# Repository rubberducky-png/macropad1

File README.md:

# rektek macropad
It has 9 keys (9 switches), a rotary encoder, and an OLED display. Each key is backlit with SK6812 MINI-E LEDs. It uses [QMK](https://qmk.fm/) firmware

## CAD Model:
Everything is connected by four M3x16mm screws and M3x5mx4mm heatset inserts. The case is printed in two parts, top and bottom.

<p align="center">
  <strong>Made in onShape</strong>
</p>

## PCB:
<p align="center">
  Schematic
</p>

<br>
<p align="center">
  PCB
</p>

<p align="center">
  <strong>Made in KiCad</strong>
</p>

## Case:

<p align="center">
  <strong>Made in onShape</strong>
</p>

## Firmware:
This Hackpad uses KMK.
#   Row 1: Rewind          Play/Pause      Fast Forward
#   Row 2: Netflix         Spotify         VS Code
#   Row 3: Left             Right           LED Mode Cycle

</p>

## Final result:
<p align="center">
 TBD
</p>
<p align="center">
    <b>HACKPAD DEMO WILL BE HERE</b>
  </a>
</p>
I really enjoyed creating my own hackpad, I learned how to create PCBs and schematics in KiCAD. There were a few mistakes in the model, but I was able to fix them pretty easily

## BOM:
Here is everything you need to create this Hackpad:
| Component | Amount |
| :--- | :---: |
| **Seeed XIAO RP2040** | 1x |
| **MX-Style switches** | 9x |
| **1N4148 Diodes** | 9x | 
| **EC11 Rotary encoder** | 1x |
| **0.91 inch OLED display** | 1x |
| **DSA keycaps** | 9x |
| **SK6812 MINI-E LED** | 12x |
| **M3x16mm screw** | 4x |
| **M3x5mx4mm heatset insert** | 4x |
| **Case** (2 printed parts) | 1x |
| **PCB** | 1x |

<hr>

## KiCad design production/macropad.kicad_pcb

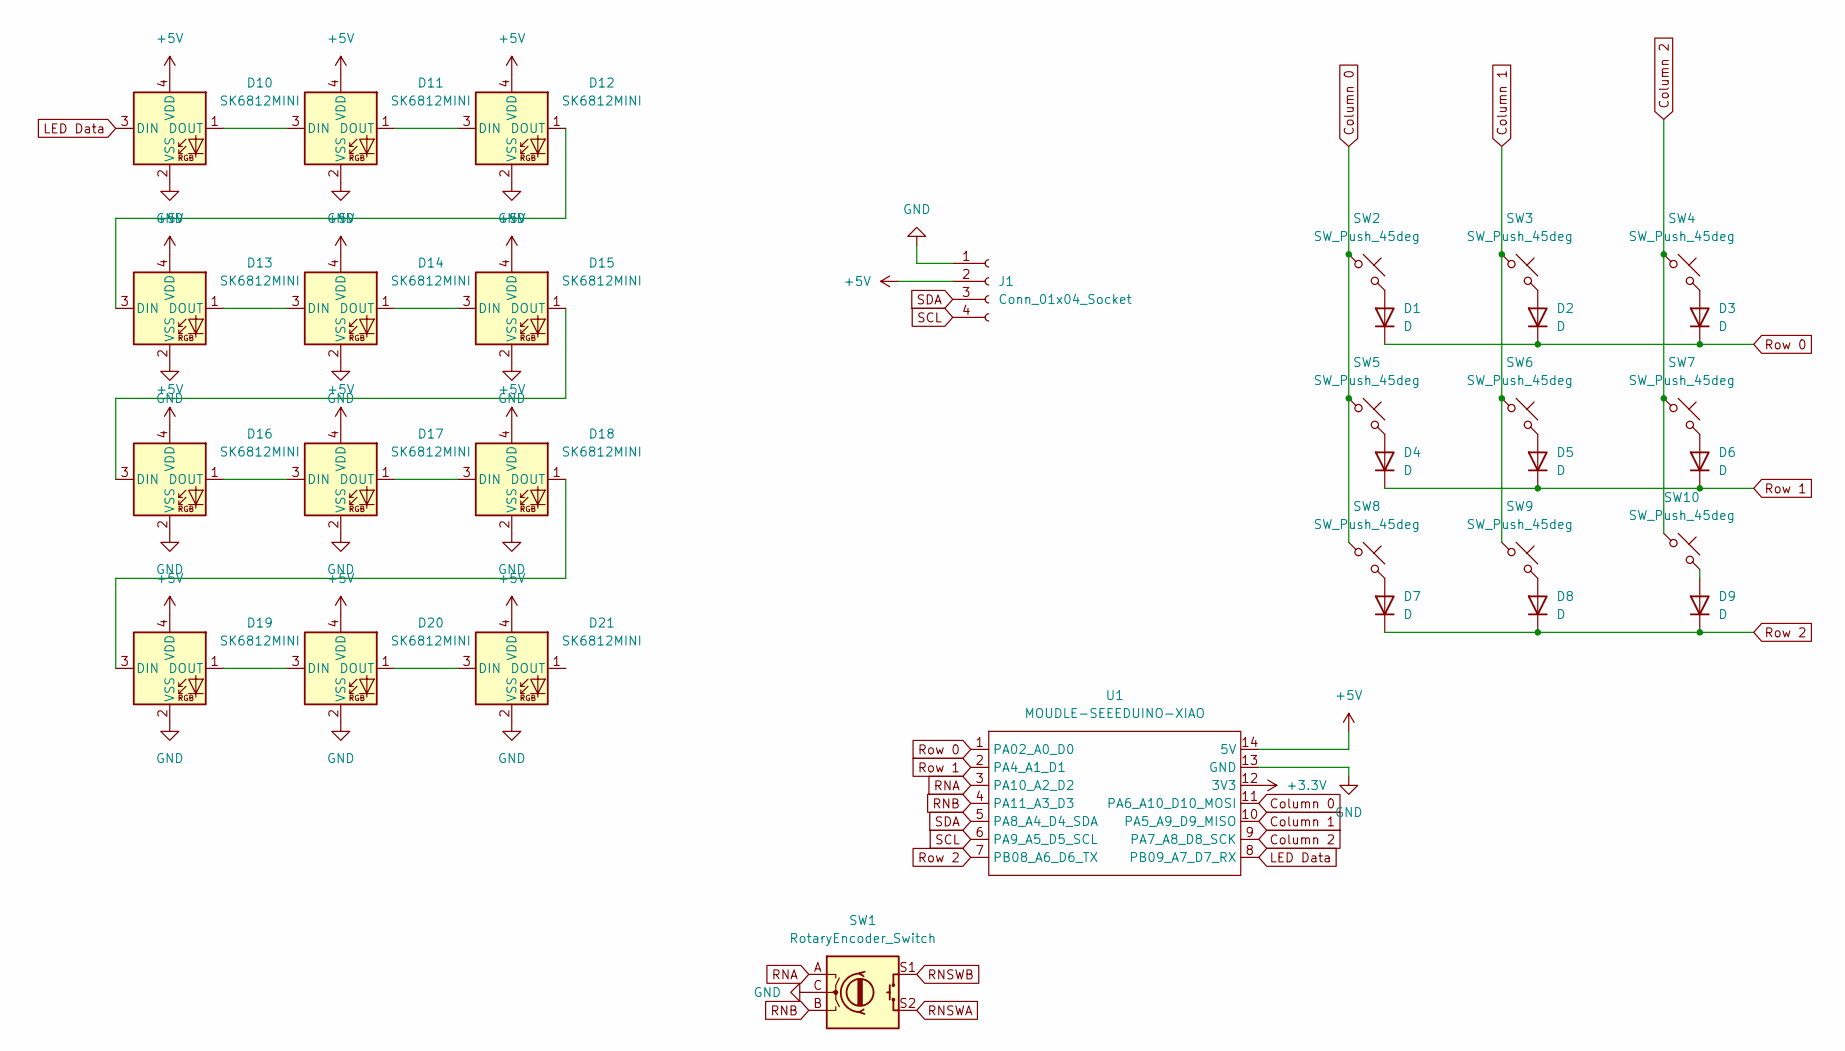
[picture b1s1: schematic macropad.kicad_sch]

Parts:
D1, D2, D3, D4, D5, D6, D7, D8, D9: D; D_DO-35_SOD27_P7.62mm_Horizontal
D10, D11, D12, D13, D14, D15, D16, D17, D18, D19, D20, D21: SK6812MINI; LED_SK6812MINI_PLCC4_3.5x3.5mm_P1.75mm
J1: Conn_01x04_Socket; SSD1306-0.91-OLED-4pin-128x32
SW1: RotaryEncoder_Switch; RotaryEncoder_Alps_EC11E-Switch_Vertical_H20mm
SW2, SW3, SW4, SW5, SW6, SW7, SW8, SW9, SW10: SW_Push_45deg; SW_Cherry_MX_1.00u_PCB
U1: MOUDLE-SEEEDUINO-XIAO; XIAO-Generic-Hybrid-14P-2.54-21X17.8MM

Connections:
+3.3V: U1.12 (3V3)
+5V: D10.4 (VDD), D11.4 (VDD), D12.4 (VDD), D13.4 (VDD), D14.4 (VDD), D15.4 (VDD), D16.4 (VDD), D17.4 (VDD), D18.4 (VDD), D19.4 (VDD), D20.4 (VDD), D21.4 (VDD), J1.2, U1.14 (5V)
Column 0: SW2.1, SW5.1, SW8.1, U1.11 (PA6_A10_D10_MOSI)
Column 1: SW3.1, SW6.1, SW9.1, U1.10 (PA5_A9_D9_MISO)
Column 2: SW4.1, SW7.1, SW10.1, U1.9 (PA7_A8_D8_SCK)
GND: D10.2 (VSS), D11.2 (VSS), D12.2 (VSS), D13.2 (VSS), D14.2 (VSS), D15.2 (VSS), D16.2 (VSS), D17.2 (VSS), D18.2 (VSS), D19.2 (VSS), D20.2 (VSS), D21.2 (VSS), J1.1, SW1.C, U1.13 (GND)
LED Data: D10.3 (DIN), U1.8 (PB09_A7_D7_RX)
unnamed: D1.2 (A), SW2.2
unnamed: D2.2 (A), SW3.2
unnamed: D3.2 (A), SW4.2
unnamed: D4.2 (A), SW5.2
unnamed: D5.2 (A), SW6.2
unnamed: D6.2 (A), SW7.2
unnamed: D7.2 (A), SW8.2
unnamed: D8.2 (A), SW9.2
unnamed: D9.2 (A), SW10.2
unnamed: D10.1 (DOUT), D11.3 (DIN)
unnamed: D11.1 (DOUT), D12.3 (DIN)
unnamed: D12.1 (DOUT), D13.3 (DIN)
unnamed: D13.1 (DOUT), D14.3 (DIN)
unnamed: D14.1 (DOUT), D15.3 (DIN)
unnamed: D15.1 (DOUT), D16.3 (DIN)
unnamed: D16.1 (DOUT), D17.3 (DIN)
unnamed: D17.1 (DOUT), D18.3 (DIN)
unnamed: D18.1 (DOUT), D19.3 (DIN)
unnamed: D19.1 (DOUT), D20.3 (DIN)
unnamed: D20.1 (DOUT), D21.3 (DIN)
RNA: SW1.A, U1.3 (PA10_A2_D2)
RNB: SW1.B, U1.4 (PA11_A3_D3)
RNSWA: SW1.S2
RNSWB: SW1.S1
Row 0: D1.1 (K), D2.1 (K), D3.1 (K), U1.1 (PA02_A0_D0)
Row 1: D4.1 (K), D5.1 (K), D6.1 (K), U1.2 (PA4_A1_D1)
Row 2: D7.1 (K), D8.1 (K), D9.1 (K), U1.7 (PB08_A6_D6_TX)
SCL: J1.4, U1.6 (PA9_A5_D5_SCL)
SDA: J1.3, U1.5 (PA8_A4_D4_SDA)

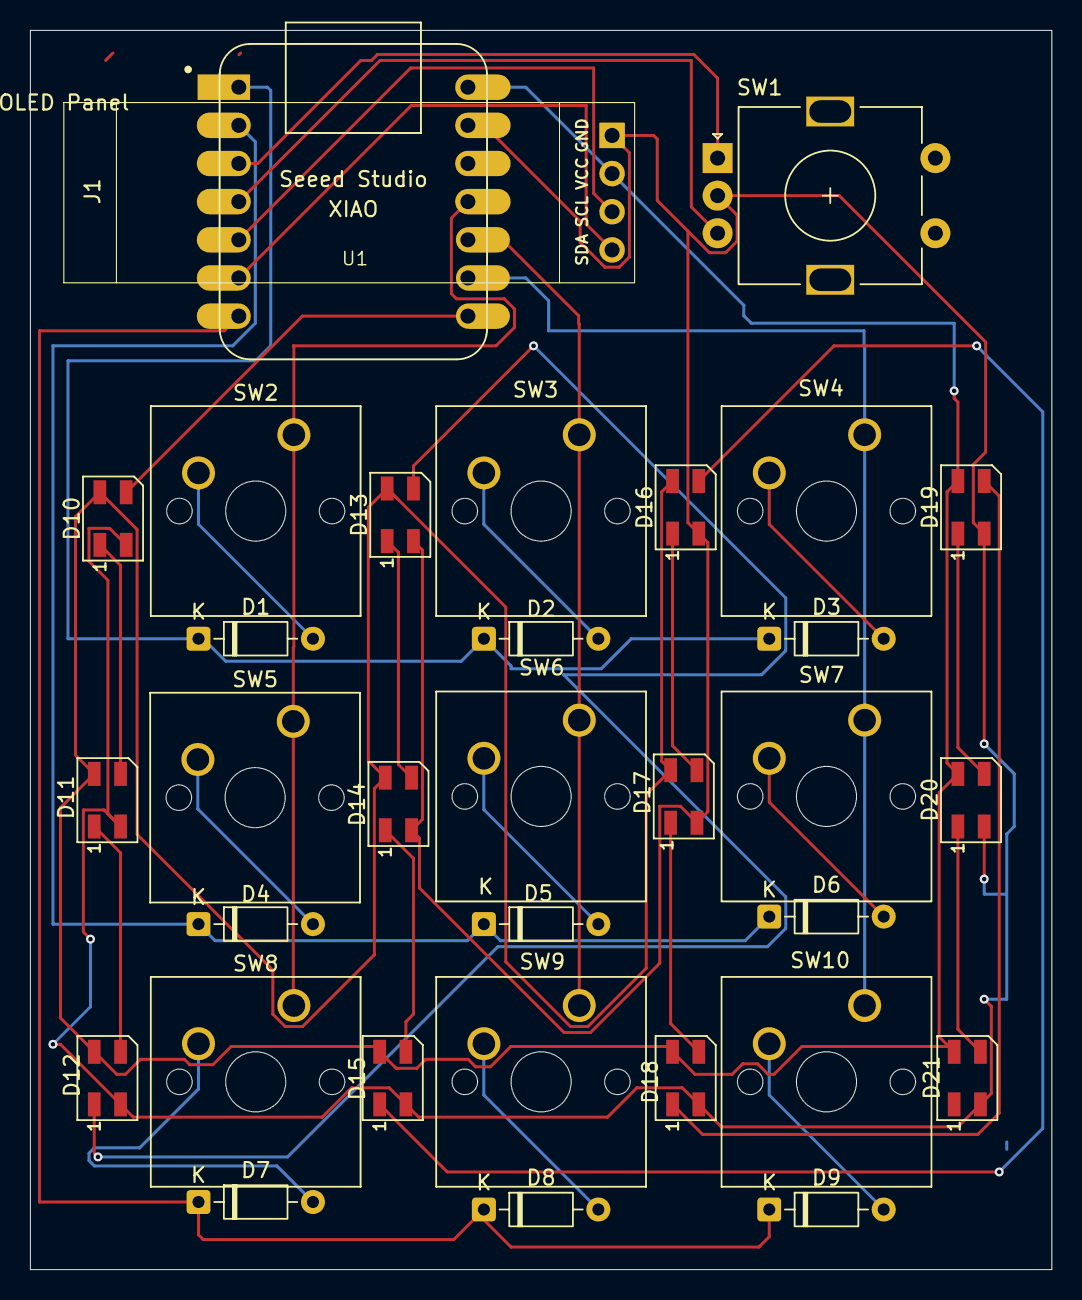
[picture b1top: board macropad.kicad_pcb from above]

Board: 2 copper layers, 68.0 x 82.5 mm, 33 parts (0 on the bottom side), 33 nets.
